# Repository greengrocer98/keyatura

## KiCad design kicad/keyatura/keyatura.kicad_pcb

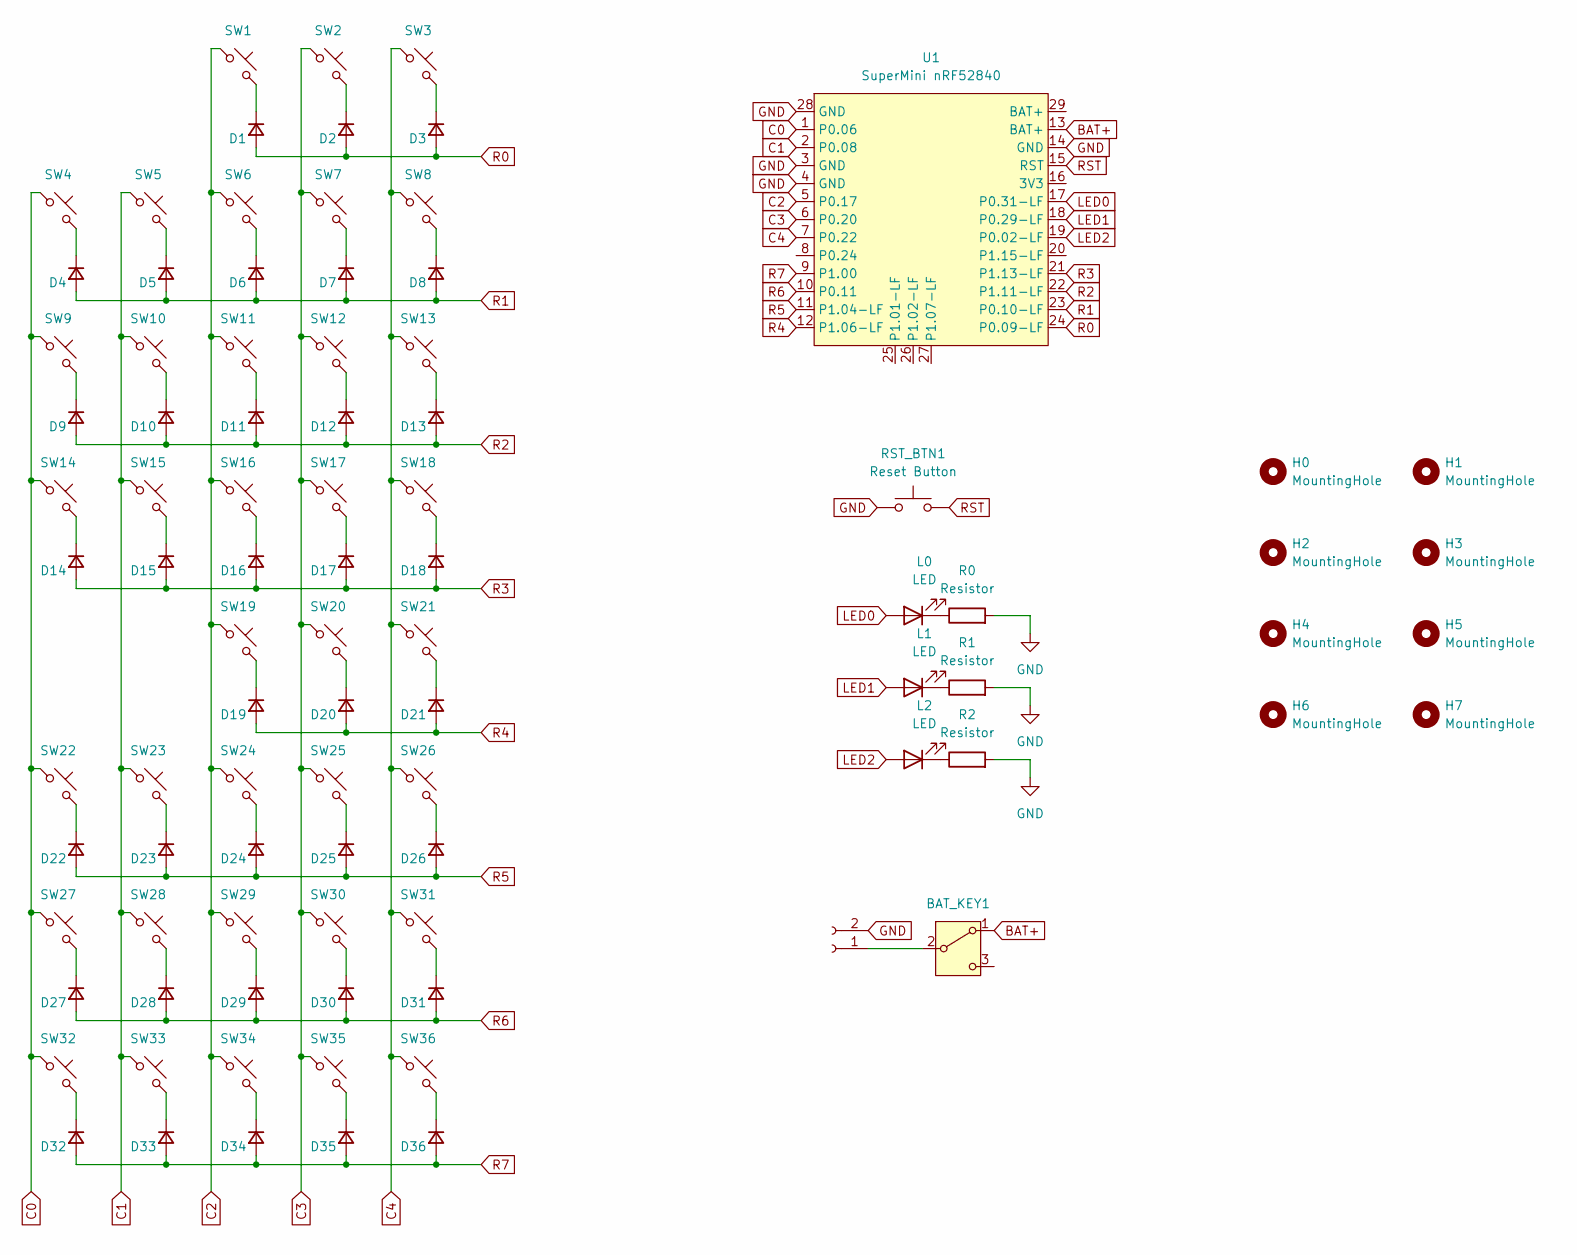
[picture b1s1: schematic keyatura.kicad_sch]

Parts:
BAT_KEY1: SW_SPDT; MSK-12C02
D1, D2, D3, D4, D5, D6, D7, D8, D9, D10, D11, D12, D13, D14, D15, D16, D17, D18, D19, D20, D21, D22, D23, D24, D25, D26, D27, D28, D29, D30, D31, D32, D33, D34, D35, D36: D; diode
H0, H1, H2, H3, H4, H5, H6, H7: MountingHole; mounting hole
J1: Battery; battery
L0, L1, L2: LED
R0, R1, R2: Resistor; resistor
RST_BTN1: Reset Button; reset button
SW1, SW2, SW3, SW4, SW5, SW6, SW7, SW8, SW9, SW10, SW11, SW12, SW13, SW14, SW15, SW16, SW17, SW18, SW19, SW20, SW21, SW22, SW23, SW24, SW25, SW26, SW27, SW28, SW29, SW30, SW31, SW32, SW33, SW34, SW35, SW36: SW_Push; SW_MX_Kailh_Choc_V1V2_HotSwap_Hybrid
U1: SuperMini nRF52840; supermini

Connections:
BAT+: BAT_KEY1.1 (A), U1.13 (BAT+)
C0: SW4.1, SW9.1, SW14.1, SW22.1, SW27.1, SW32.1, U1.1 (P0.06)
C1: SW5.1, SW10.1, SW15.1, SW23.1, SW28.1, SW33.1, U1.2 (P0.08)
C2: SW1.1, SW6.1, SW11.1, SW16.1, SW19.1, SW24.1, SW29.1, SW34.1, U1.5 (P0.17)
C3: SW2.1, SW7.1, SW12.1, SW17.1, SW20.1, SW25.1, SW30.1, SW35.1, U1.6 (P0.20)
C4: SW3.1, SW8.1, SW13.1, SW18.1, SW21.1, SW26.1, SW31.1, SW36.1, U1.7 (P0.22)
GND: J1.2, R0.2, R1.2, R2.2, RST_BTN1.1, U1.3 (GND), U1.4 (GND), U1.14 (GND), U1.28 (GND)
LED0: L0.2 (A), U1.17 (P0.31-LF)
LED1: L1.2 (A), U1.18 (P0.29-LF)
LED2: L2.2 (A), U1.19 (P0.02-LF)
unnamed: BAT_KEY1.2 (B), J1.1
unnamed: D1.1 (K), SW1.2
unnamed: D2.1 (K), SW2.2
unnamed: D3.1 (K), SW3.2
unnamed: D4.1 (K), SW4.2
unnamed: D5.1 (K), SW5.2
unnamed: D6.1 (K), SW6.2
unnamed: D7.1 (K), SW7.2
unnamed: D8.1 (K), SW8.2
unnamed: D9.1 (K), SW9.2
unnamed: D10.1 (K), SW10.2
unnamed: D11.1 (K), SW11.2
unnamed: D12.1 (K), SW12.2
unnamed: D13.1 (K), SW13.2
unnamed: D14.1 (K), SW14.2
unnamed: D15.1 (K), SW15.2
unnamed: D16.1 (K), SW16.2
unnamed: D17.1 (K), SW17.2
unnamed: D18.1 (K), SW18.2
unnamed: D19.1 (K), SW19.2
unnamed: D20.1 (K), SW20.2
unnamed: D21.1 (K), SW21.2
unnamed: D22.1 (K), SW22.2
unnamed: D23.1 (K), SW23.2
unnamed: D24.1 (K), SW24.2
unnamed: D25.1 (K), SW25.2
unnamed: D26.1 (K), SW26.2
unnamed: D27.1 (K), SW27.2
unnamed: D28.1 (K), SW28.2
unnamed: D29.1 (K), SW29.2
unnamed: D30.1 (K), SW30.2
unnamed: D31.1 (K), SW31.2
unnamed: D32.1 (K), SW32.2
unnamed: D33.1 (K), SW33.2
unnamed: D34.1 (K), SW34.2
unnamed: D35.1 (K), SW35.2
unnamed: D36.1 (K), SW36.2
unnamed: L0.1 (K), R0.1
unnamed: L1.1 (K), R1.1
unnamed: L2.1 (K), R2.1
R0: D1.2 (A), D2.2 (A), D3.2 (A), U1.24 (P0.09-LF)
R1: D4.2 (A), D5.2 (A), D6.2 (A), D7.2 (A), D8.2 (A), U1.23 (P0.10-LF)
R2: D9.2 (A), D10.2 (A), D11.2 (A), D12.2 (A), D13.2 (A), U1.22 (P1.11-LF)
R3: D14.2 (A), D15.2 (A), D16.2 (A), D17.2 (A), D18.2 (A), U1.21 (P1.13-LF)
R4: D19.2 (A), D20.2 (A), D21.2 (A), U1.12 (P1.06-LF)
R5: D22.2 (A), D23.2 (A), D24.2 (A), D25.2 (A), D26.2 (A), U1.11 (P1.04-LF)
R6: D27.2 (A), D28.2 (A), D29.2 (A), D30.2 (A), D31.2 (A), U1.10 (P0.11)
R7: D32.2 (A), D33.2 (A), D34.2 (A), D35.2 (A), D36.2 (A), U1.9 (P1.00)
RST: RST_BTN1.2, U1.15 (RST)

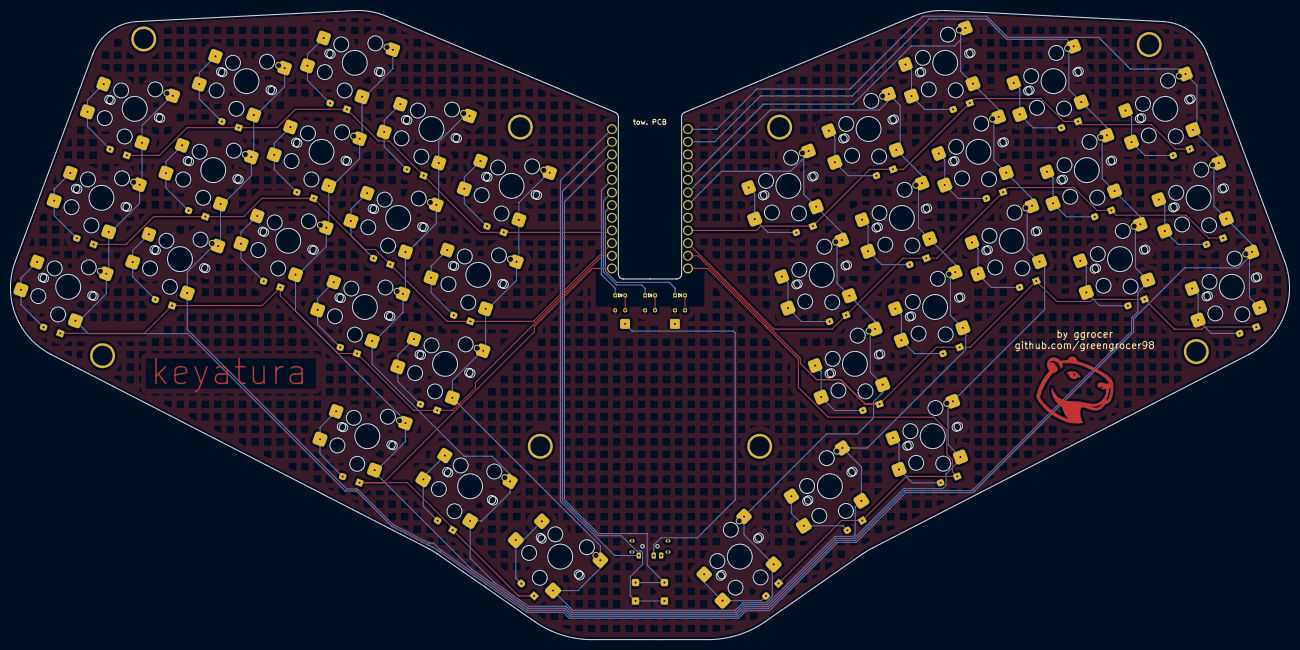
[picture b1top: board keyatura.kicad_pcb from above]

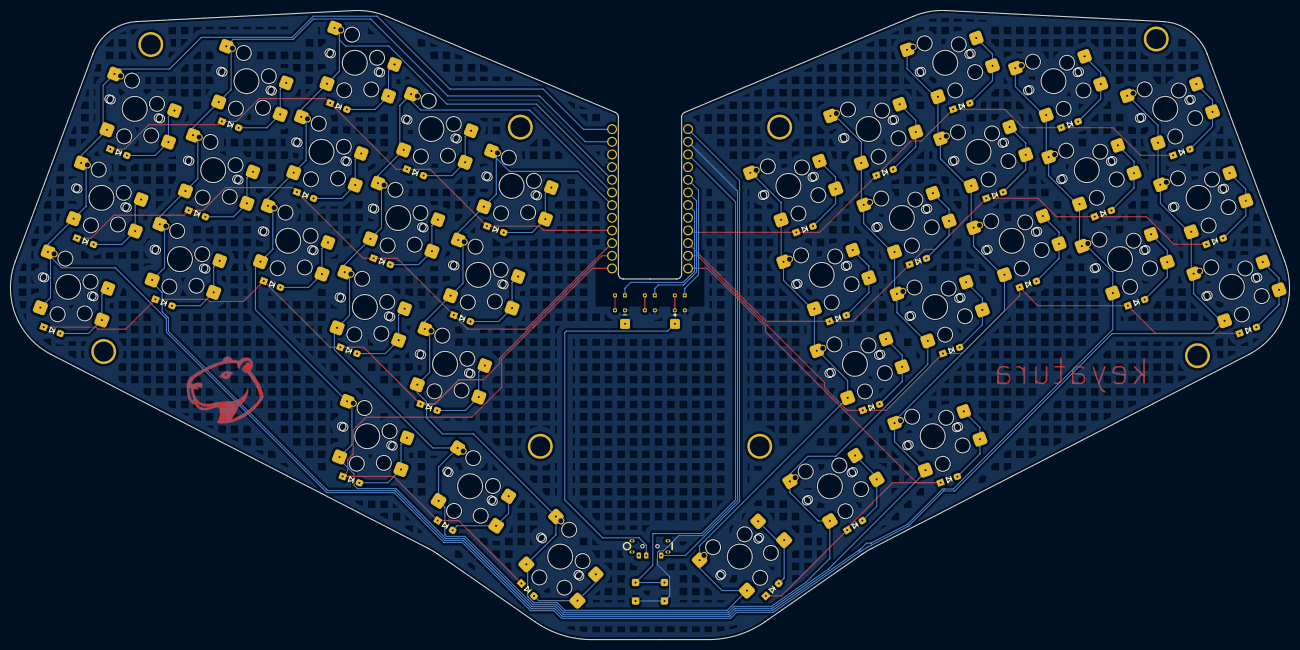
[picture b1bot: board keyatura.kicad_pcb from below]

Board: 2 copper layers, 256.5 x 126.2 mm, 91 parts (37 on the bottom side), 59 nets.

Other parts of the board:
G1: LOGO

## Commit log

2025-04-03 added support of cirque trackpad
2025-04-03 update overlay for left side for actions build
2025-04-19 changed trackpad parameters and sensetivity
2025-05-16 added rgb widget
2025-05-16 update keymap
2025-05-19 updated keymap
2025-05-20 yet another updated keymap
2025-06-10 minor updates in keymap
2025-06-17 added mouse to dongle setup
2025-06-19 updates in mouse key and sensor configuration
2025-06-27 changes in combos
2025-07-01 esb communication
2025-07-01 fix column gpios on right side
2025-10-09 fixed fatal bug of connected B- and B+ while turning off battery
